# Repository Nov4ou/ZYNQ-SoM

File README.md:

# ZYNQ-SoM

An open-source Zynq-7000 system-on-module, designed in KiCad. The Rev B boards have been assembled and tested.

## Photos

## What is on the board

- AMD/Xilinx XC7Z010-1CLG400C
- 512 MiB DDR3 (Micron MT41K256M16)
- 32 MiB QSPI NOR flash (Winbond W25Q256)
- 33.3333 MHz PS reference clock
- Two Panasonic AXK580137YG 80-pin board-to-board receptacles
- 50 mm × 40 mm, 6-layer PCB
- Separate PL Bank 34 and Bank 35 I/O voltage inputs
- 5 V module input with on-board power rails

The bottom-side silkscreen labels the connectors `PL IO` and `PS IO`. J402 carries PS MIO, configuration/JTAG, and PL Bank 35. J403 carries PL Bank 34 and module power-related pins.

## Files

```text
hardware/kicad/        KiCad project, schematic, PCB, symbols, footprints, and 3D models
docs/                  Schematic PDF, schematic page images, photos, and connector lengths
production/bom/        BOM exported from KiCad
production/gerbers/    Gerber and drill files
```

Open [hardware/kicad/ZYNQ-SoM.kicad_pro](hardware/kicad/ZYNQ-SoM.kicad_pro) with KiCad 10.0 or newer. Project symbols, footprints, and 3D models are referenced relative to `${KIPRJMOD}`, so no global custom-library setup is required.

## Useful files

- [SoM connector routing lengths](docs/connector-routing-lengths.md)
- [Machine-readable routing lengths](docs/connector-routing-lengths.csv)
- [Schematic PDF](docs/ZYNQ-SoM-schematic.pdf)
- [Gerber ZIP](production/gerbers/ZYNQ-SoM.zip)
- [BOM](production/bom/ZYNQ-SoM.csv)

The connector length table is for carrier-board length matching. It uses KiCad Net Inspector style lengths for the SoM-side routing; connector contact length and carrier-board routing are not included.

## Notes

- The checked-in Gerbers are the fabrication files for this revision.
- Review the KiCad source before ordering boards or changing parts.

## License

Released under the CERN Open Hardware Licence Version 2 - Permissive (`CERN-OHL-P-2.0`). See [LICENSE](LICENSE).

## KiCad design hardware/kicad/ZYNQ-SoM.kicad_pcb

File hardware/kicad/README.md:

# KiCad source

Open `ZYNQ-SoM.kicad_pro` with KiCad 10.0 or newer.

- `ZYNQ-SoM.kicad_sch` is the root schematic.
- `sheets/` contains the hierarchical schematic sheets.
- `ZYNQ-SoM.kicad_pcb` is the six-layer board layout.
- `ZYNQ-SoM.kicad_dru` contains project design rules.
- `lib/` contains the project-local KiCad symbols, `.pretty` footprint library, and 3D models.

Library tables use `${KIPRJMOD}` paths, so the project should be portable after cloning.

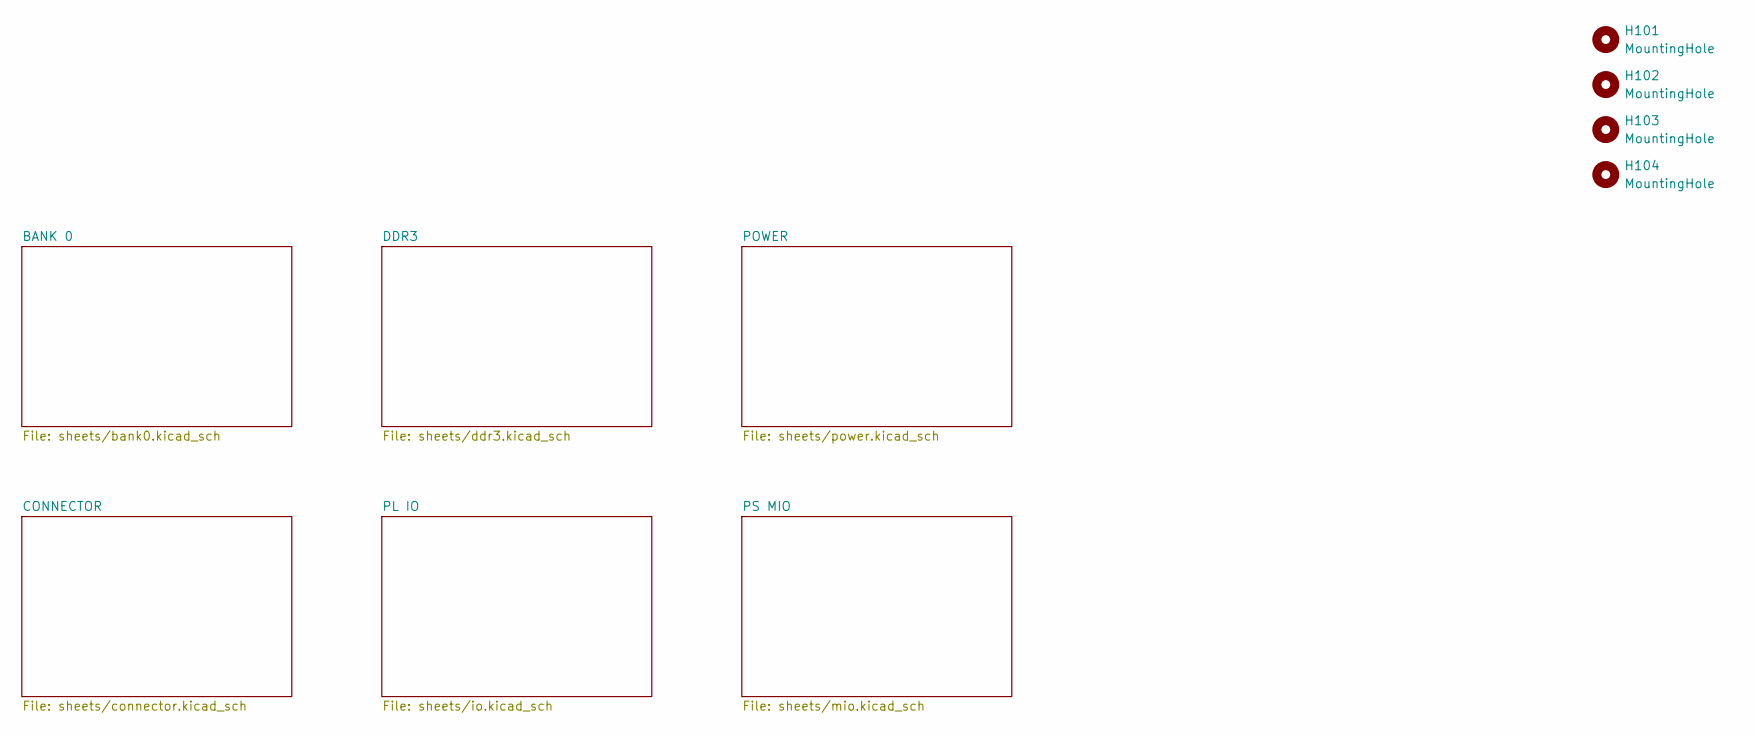
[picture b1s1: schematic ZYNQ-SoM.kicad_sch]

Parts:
H101, H102, H103, H104: MountingHole; MountingHole_2.2mm_M2

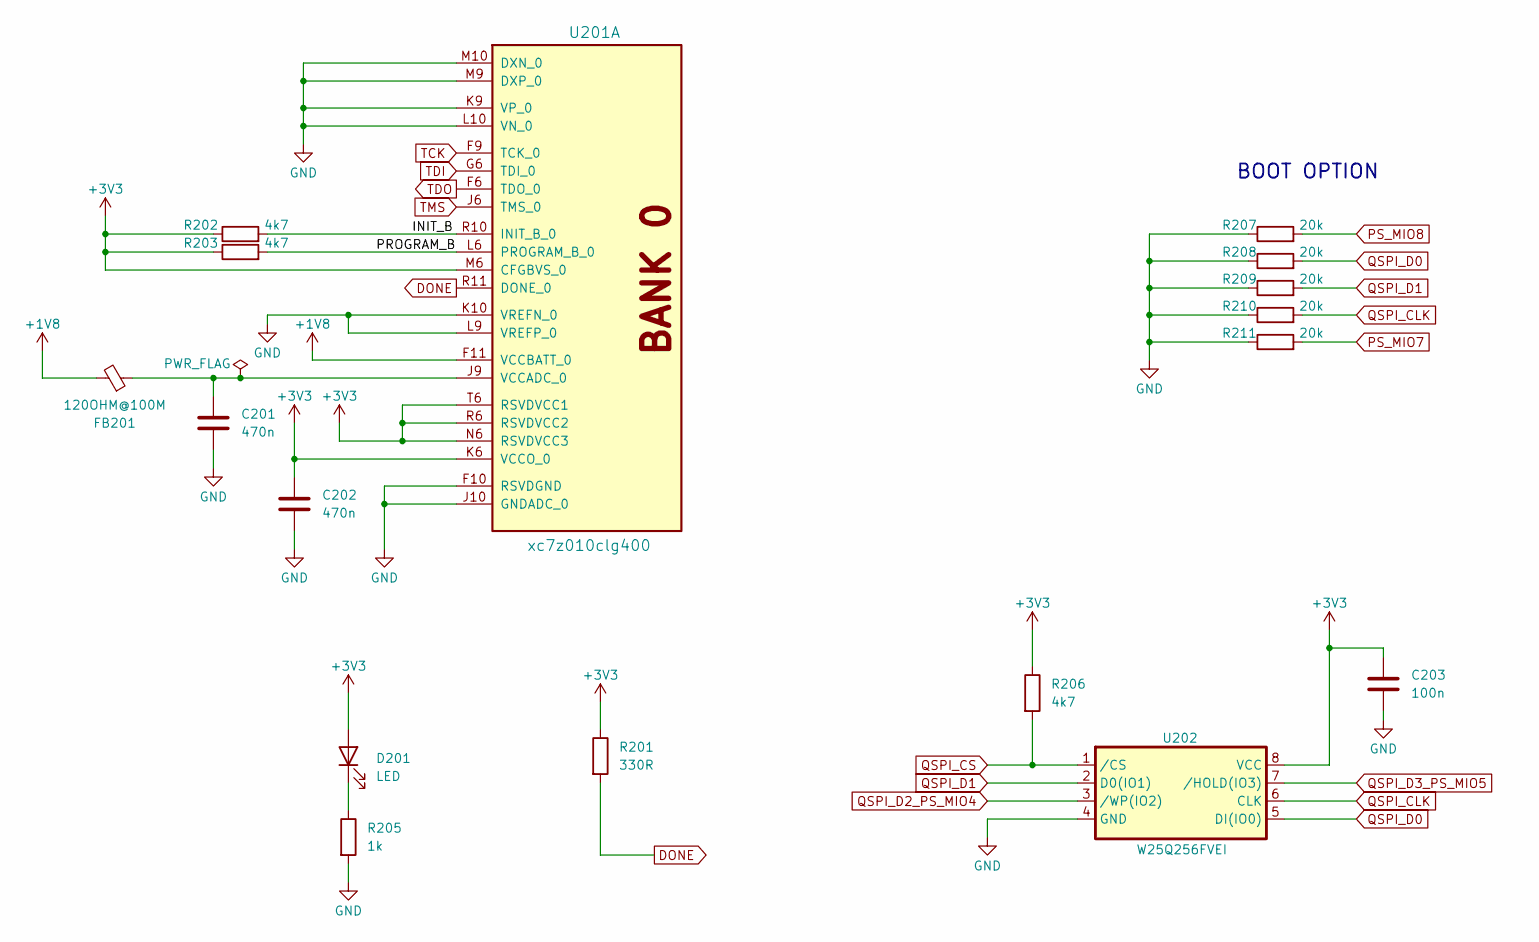
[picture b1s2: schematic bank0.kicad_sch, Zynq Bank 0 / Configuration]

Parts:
C201, C202: 470n; C_0402_1005Metric
C203: 100n; C_0402_1005Metric
D201: LED; LED_0603_1608Metric
FB201: 120OHM@100M; L_0402_1005Metric
R201: 330R; R_0402_1005Metric
R202, R203, R206: 4k7; R_0402_1005Metric
R205: 1k; R_0402_1005Metric
R207, R208, R209, R210, R211: 20k; R_0402_1005Metric
U201: xc7z010clg400; Xilinx_CLG400
U202: W25Q256FVEI; SON127P800X600X80-9N-D

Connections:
+1V8: FB201.2, U201.F11 (VCCBATT_0); also elsewhere on the board
+3V3: C202.1, C203.1, D201.2 (A), R201.1, R202.1, R203.1, R206.1, U201.K6 (VCCO_0), U201.M6 (CFGBVS_0), U201.N6 (RSVDVCC3), U201.R6 (RSVDVCC2), U201.T6 (RSVDVCC1), U202.8 (VCC); also elsewhere on the board
/BANK 0/INIT_B: R202.2, U201.R10 (INIT_B_0)
/BANK 0/PROGRAM_B: R203.2, U201.L6 (PROGRAM_B_0)
DONE: R201.2, U201.R11 (DONE_0); also elsewhere on the board
GND: C201.2, C202.2, C203.2, R205.2, R207.1, R208.1, R209.1, R210.1, R211.1, U201.F10 (RSVDGND), U201.J10 (GNDADC_0), U201.K9 (VP_0), U201.K10 (VREFN_0), U201.L9 (VREFP_0), U201.L10 (VN_0), U201.M9 (DXP_0), U201.M10 (DXN_0), U202.4 (GND), U202.9 (GND); also elsewhere on the board
unnamed: D201.1 (K), R205.1
unnamed: C201.1, FB201.1, U201.J9 (VCCADC_0)
PS_MIO7: R211.2; also elsewhere on the board
PS_MIO8: R207.2; also elsewhere on the board
QSPI_CLK: R210.2, U202.6 (CLK); also elsewhere on the board
QSPI_CS: R206.2, U202.1 (/CS); also elsewhere on the board
QSPI_D0: R208.2, U202.5 (DI(IO0)); also elsewhere on the board
QSPI_D1: R209.2, U202.2 (D0(IO1)); also elsewhere on the board
QSPI_D2_PS_MIO4: U202.3 (/WP(IO2)); also elsewhere on the board
QSPI_D3_PS_MIO5: U202.7 (/HOLD(IO3)); also elsewhere on the board
TCK: U201.F9 (TCK_0); also elsewhere on the board
TDI: U201.G6 (TDI_0); also elsewhere on the board
TDO: U201.F6 (TDO_0); also elsewhere on the board
TMS: U201.J6 (TMS_0); also elsewhere on the board

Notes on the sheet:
BOOT OPTION

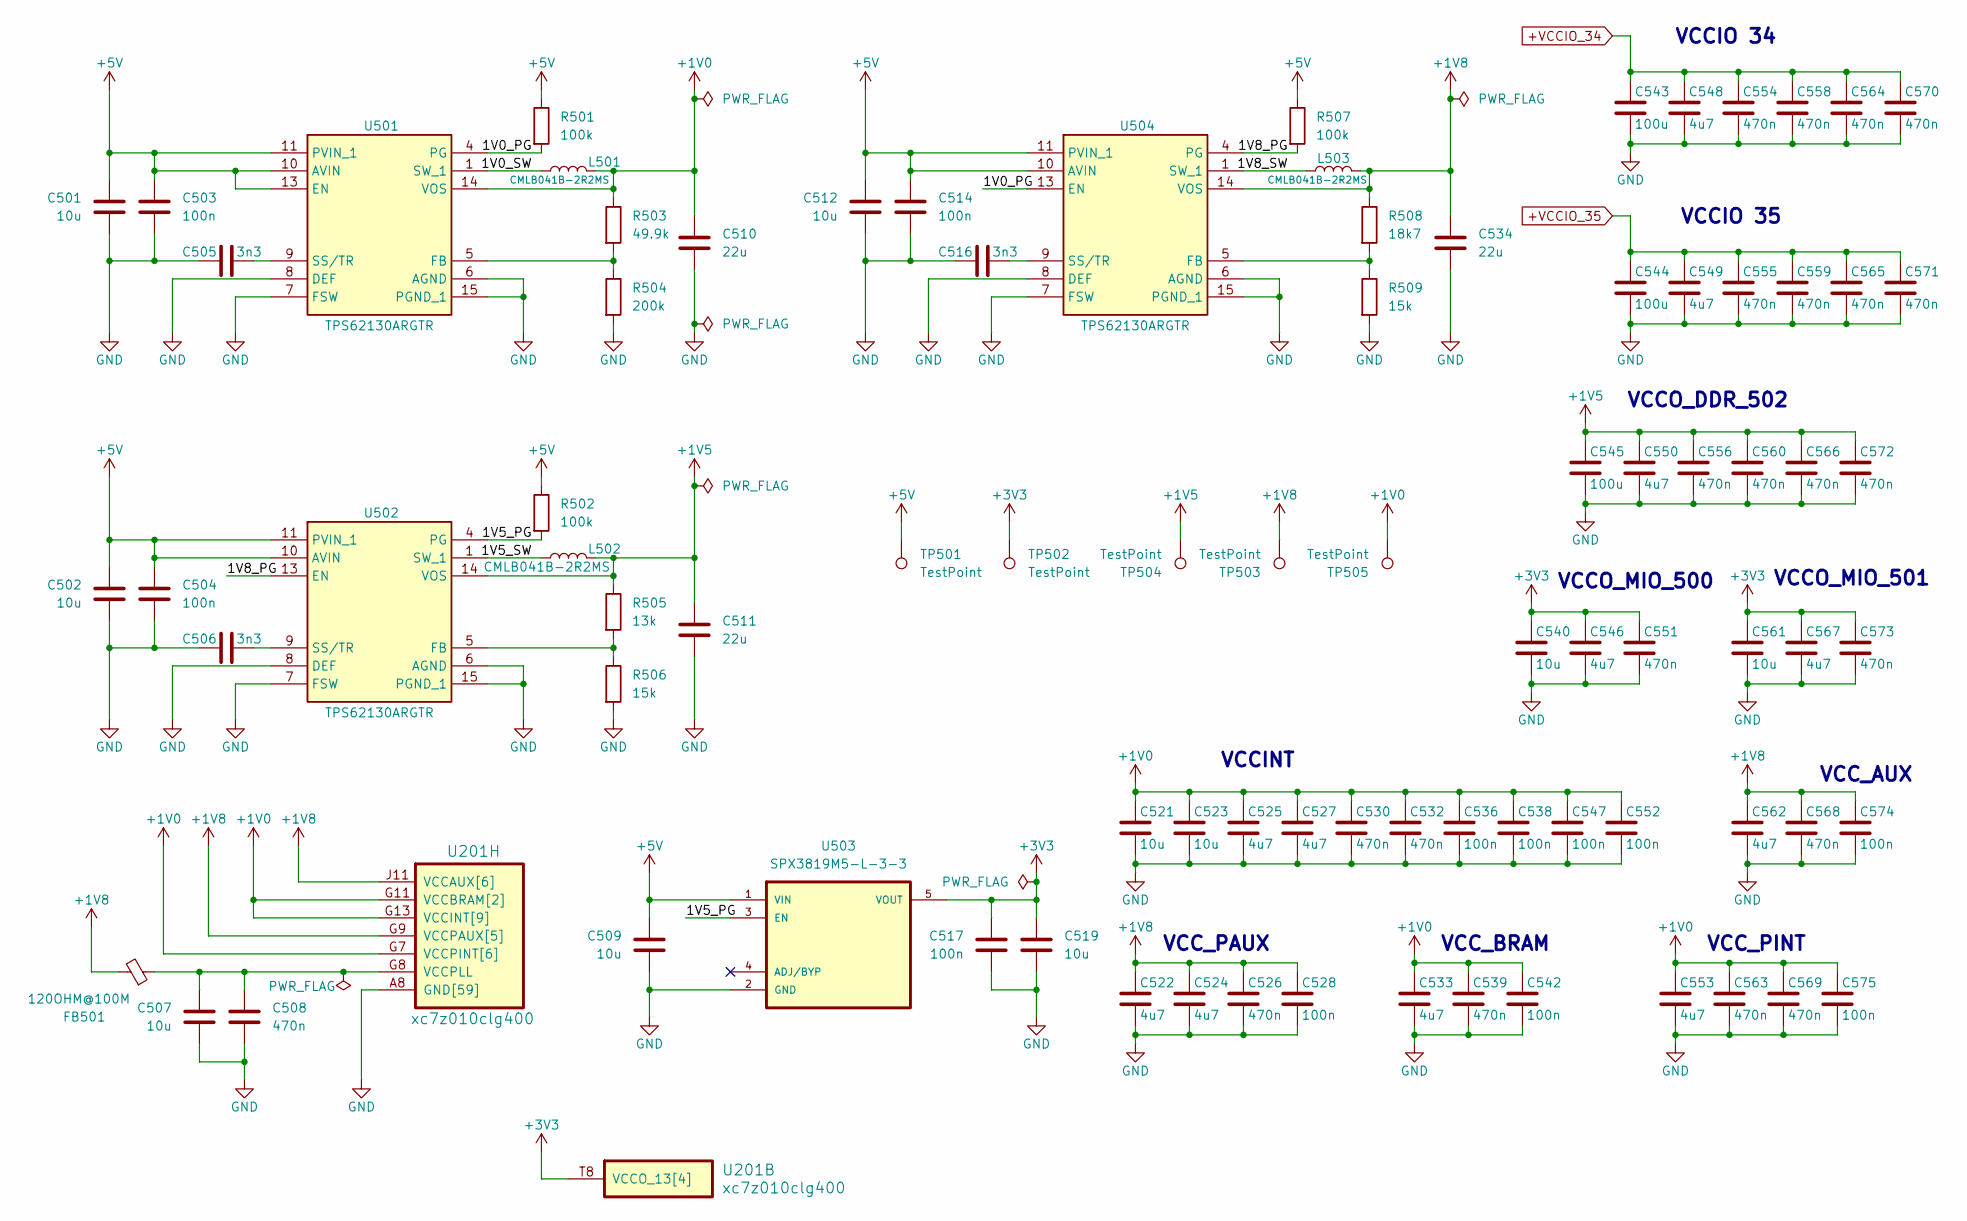
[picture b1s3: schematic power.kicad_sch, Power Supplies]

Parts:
C501, C502, C509, C512, C519, C521, C523, C561: 10u; C_0805_2012Metric
C503, C504, C514, C517, C528, C536, C538, C542, C547, C552, C574, C575: 100n; C_0402_1005Metric
C505, C506, C516: 3n3; C_0402_1005Metric
C507, C540: 10u; C_0603_1608Metric
C508, C526, C530, C532, C539, C551, C554, C555, C556, C558, C559, C560, C563, C564, C565, C566, C568, C569, C570, C571, C572, C573: 470n; C_0402_1005Metric
C510, C511, C534: 22u; C_0805_2012Metric
C522, C524, C525, C527, C533, C546, C548, C549, C550, C553, C562, C567: 4u7; C_0603_1608Metric
C543, C544, C545: 100u; C_1206_3216Metric
FB501: 120OHM@100M; L_0402_1005Metric
L501, L502, L503: CMLB041B-2R2MS; IND_CMLB041B-1R0MS
R501, R502, R507: 100k; R_0402_1005Metric
R503: 49.9k; R_0402_1005Metric
R504: 200k; R_0402_1005Metric
R505: 13k; R_0402_1005Metric
R506, R509: 15k; R_0402_1005Metric
R508: 18k7; R_0402_1005Metric
TP501, TP502, TP503, TP504, TP505: TestPoint; TestPoint_Pad_D1.0mm
U201: xc7z010clg400; Xilinx_CLG400
U501, U502, U504: TPS62130ARGTR; QFN50P300X300X100-17N-D; Manufacturer_Part_Number TPS62130ARGTR; Mouser Part Number 595-TPS62130ARGTR
U503: SPX3819M5-L-3-3; MPN SPX3819M5-L-3-3

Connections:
+1V0: C510.1, C521.1, C523.1, C525.1, C527.1, C530.1, C532.1, C533.1, C536.1, C538.1, C539.1, C542.1, C547.1, C552.1, C553.1, C563.1, C569.1, C575.1, L501.2, R503.1, TP505.1 (1_1), U201.G7 (VCCPINT[6]), U201.G11 (VCCBRAM[2]), U201.G13 (VCCINT[9]), U201.H10 (VCCBRAM[2]), U201.H12 (VCCINT[9]), U201.J7 (VCCPINT[6]), U201.J13 (VCCINT[9]), U201.K12 (VCCINT[9]), U201.L7 (VCCPINT[6]), U201.L13 (VCCINT[9]), U201.M12 (VCCINT[9]), U201.N7 (VCCPINT[6]), U201.N13 (VCCINT[9]), U201.P8 (VCCPINT[6]), U201.P12 (VCCINT[9]), U201.R7 (VCCPINT[6]), U201.R13 (VCCINT[9]), U501.14 (VOS)
+1V5: C511.1, C545.1, C550.1, C556.1, C560.1, C566.1, C572.1, L502.2, R505.1, TP504.1 (1_1), U502.14 (VOS); also elsewhere on the board
+1V8: C522.1, C524.1, C526.1, C528.1, C534.1, C562.1, C568.1, C574.1, FB501.2, L503.2, R508.1, TP503.1 (1_1), U201.F8 (VCCPAUX[5]), U201.G9 (VCCPAUX[5]), U201.H8 (VCCPAUX[5]), U201.J11 (VCCAUX[6]), U201.K8 (VCCPAUX[5]), U201.L11 (VCCAUX[6]), U201.M8 (VCCPAUX[5]), U201.N9 (VCCAUX[6]), U201.N11 (VCCAUX[6]), U201.P10 (VCCAUX[6]), U201.R9 (VCCAUX[6]), U504.14 (VOS); also elsewhere on the board
+3V3: C517.1, C519.1, C540.1, C546.1, C551.1, C561.1, C567.1, C573.1, TP502.1 (1_1), U201.T8 (VCCO_13[4]), U201.U11 (VCCO_13[4]), U201.W7 (VCCO_13[4]), U201.Y10 (VCCO_13[4]), U503.5 (VOUT); also elsewhere on the board
+5V: C501.1, C502.1, C503.1, C504.1, C509.1, C512.1, C514.1, R501.1, R502.1, R507.1, TP501.1 (1_1), U501.10 (AVIN), U501.11 (PVIN_1), U501.12 (PVIN_2), U501.13 (EN), U502.10 (AVIN), U502.11 (PVIN_1), U502.12 (PVIN_2), U503.1 (VIN), U504.10 (AVIN), U504.11 (PVIN_1), U504.12 (PVIN_2); also elsewhere on the board
+VCCIO_34: C543.1, C548.1, C554.1, C558.1, C564.1, C570.1; also elsewhere on the board
+VCCIO_35: C544.1, C549.1, C555.1, C559.1, C565.1, C571.1; also elsewhere on the board
/POWER/1V0_PG: R501.2, U501.4 (PG), U504.13 (EN)
/POWER/1V0_SW: L501.1, U501.1 (SW_1), U501.2 (SW_2), U501.3 (SW_3)
/POWER/1V5_PG: R502.2, U502.4 (PG), U503.3 (EN)
/POWER/1V5_SW: L502.1, U502.1 (SW_1), U502.2 (SW_2), U502.3 (SW_3)
/POWER/1V8_PG: R507.2, U502.13 (EN), U504.4 (PG)
/POWER/1V8_SW: L503.1, U504.1 (SW_1), U504.2 (SW_2), U504.3 (SW_3)
GND: C501.2, C502.2, C503.2, C504.2, C505.1, C506.1, C507.2, C508.2, C509.2, C510.2, C511.2, C512.2, C514.2, C516.1, C517.2, C519.2, C521.2, C522.2, C523.2, C524.2, C525.2, C526.2, C527.2, C528.2, C530.2, C532.2, C533.2, C534.2, C536.2, C538.2, C539.2, C540.2, C542.2, C543.2, C544.2, C545.2, C546.2, C547.2, C548.2, C549.2, C550.2, C551.2, C552.2, C553.2, C554.2, C555.2, C556.2, C558.2, C559.2, C560.2, C561.2, C562.2, C563.2, C564.2, C565.2, C566.2, C567.2, C568.2, C569.2, C570.2, C571.2, C572.2, C573.2, C574.2, C575.2, R504.2, R506.2, R509.2, U201.A8 (GND[59]), U201.A18 (GND[59]), U201.B1 (GND[59]), U201.B11 (GND[59]), U201.C4 (GND[59]), U201.C9 (GND[59]), U201.C14 (GND[59]), U201.D17 (GND[59]), U201.E10 (GND[59]), U201.E20 (GND[59]), U201.F3 (GND[59]), U201.F7 (GND[59]), U201.G10 (GND[59]), U201.G12 (GND[59]), U201.G16 (GND[59]), U201.H7 (GND[59]), U201.H9 (GND[59]), U201.H11 (GND[59]), U201.H13 (GND[59]), U201.H19 (GND[59]), U201.J2 (GND[59]), U201.J8 (GND[59]), U201.J12 (GND[59]), U201.K5 (GND[59]), U201.K7 (GND[59]), U201.K11 (GND[59]), U201.K13 (GND[59]), U201.K15 (GND[59]), U201.L8 (GND[59]), U201.L12 (GND[59]), U201.L18 (GND[59]), U201.M1 (GND[59]), U201.M7 (GND[59]), U201.M11 (GND[59]), U201.M13 (GND[59]), U201.N4 (GND[59]), U201.N8 (GND[59]), U201.N10 (GND[59]), U201.N12 (GND[59]), U201.N14 (GND[59]), U201.P7 (GND[59]), U201.P9 (GND[59]), U201.P11 (GND[59]), U201.P13 (GND[59]), U201.P17 (GND[59]), U201.R8 (GND[59]), U201.R12 (GND[59]), U201.R20 (GND[59]), U201.T3 (GND[59]), U201.T7 (GND[59]), U201.T13 (GND[59]), U201.U6 (GND[59]), U201.U16 (GND[59]), U201.V9 (GND[59]), U201.V19 (GND[59]), U201.W2 (GND[59]), U201.W12 (GND[59]), U201.Y5 (GND[59]), U201.Y15 (GND[59]), U501.6 (AGND), U501.7 (FSW), U501.8 (DEF), U501.15 (PGND_1), U501.16 (PGND_2), U501.17 (EP), U502.6 (AGND), U502.7 (FSW), U502.8 (DEF), U502.15 (PGND_1), U502.16 (PGND_2), U502.17 (EP), U503.2 (GND), U504.6 (AGND), U504.7 (FSW), U504.8 (DEF), U504.15 (PGND_1), U504.16 (PGND_2), U504.17 (EP); also elsewhere on the board
unnamed: C507.1, C508.1, FB501.1, U201.G8 (VCCPLL)
unnamed: R503.2, R504.1, U501.5 (FB)
unnamed: C505.2, U501.9 (SS/TR)
unnamed: R505.2, R506.1, U502.5 (FB)
unnamed: C506.2, U502.9 (SS/TR)
unnamed: R508.2, R509.1, U504.5 (FB)
unnamed: C516.2, U504.9 (SS/TR)

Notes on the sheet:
VCC_BRAM
VCCINT
VCCO_DDR_502
VCC_PAUX
VCC_PINT
VCCO_MIO_501
VCCIO 35
VCCIO 34
VCC_AUX
VCCO_MIO_500

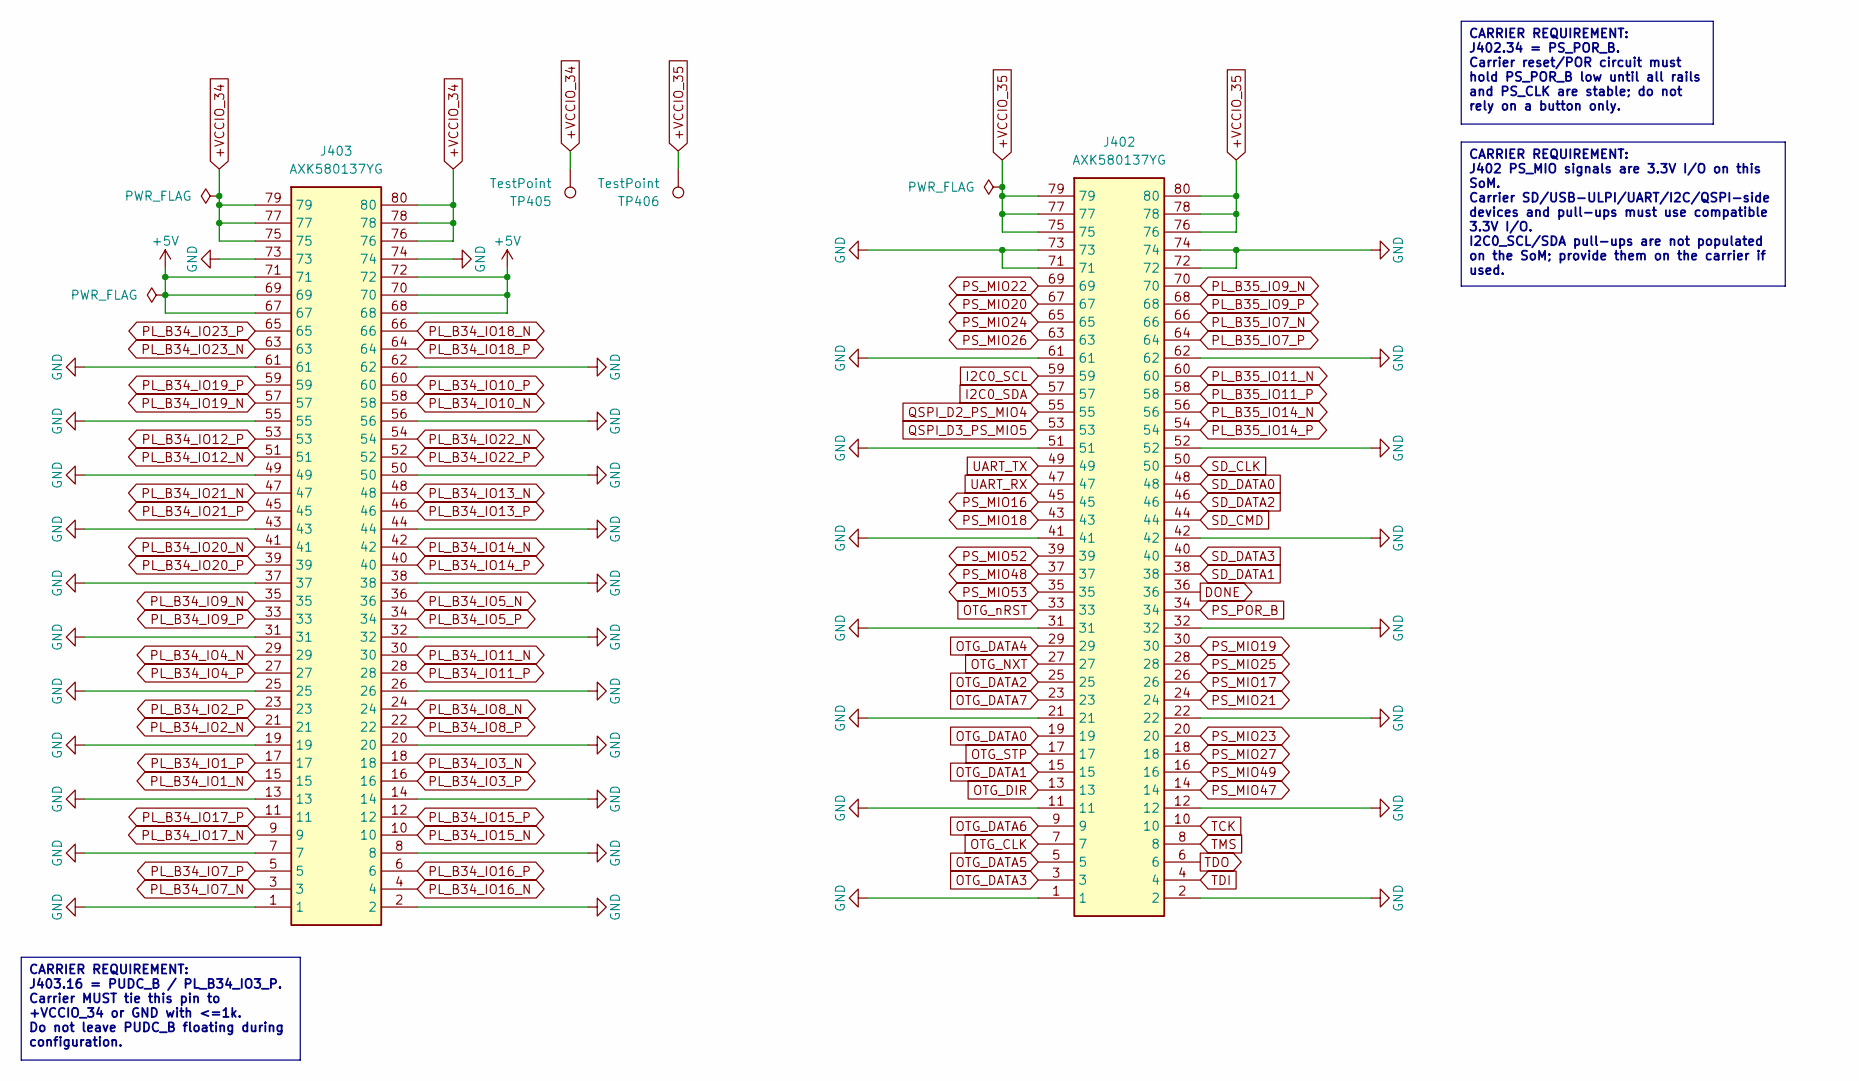
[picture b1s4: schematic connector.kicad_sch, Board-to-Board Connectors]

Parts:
J402, J403: AXK580137YG; Manufacturer_Part_Number AXK580137YG; Mouser Part Number 769-AXK580137YG
TP405, TP406: TestPoint; TestPoint_Pad_D1.0mm

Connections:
+5V: J403.67, J403.68, J403.69, J403.70, J403.71, J403.72; also elsewhere on the board
+VCCIO_34: J403.75, J403.76, J403.77, J403.78, J403.79, J403.80, TP405.1 (1_1); also elsewhere on the board
+VCCIO_35: J402.75, J402.76, J402.77, J402.78, J402.79, J402.80, TP406.1 (1_1); also elsewhere on the board
DONE: J402.36; also elsewhere on the board
GND: J402.1, J402.2, J402.11, J402.12, J402.21, J402.22, J402.31, J402.32, J402.41, J402.42, J402.51, J402.52, J402.61, J402.62, J402.71, J402.72, J402.73, J402.74, J403.1, J403.2, J403.7, J403.8, J403.13, J403.14, J403.19, J403.20, J403.25, J403.26, J403.31, J403.32, J403.37, J403.38, J403.43, J403.44, J403.49, J403.50, J403.55, J403.56, J403.61, J403.62, J403.73, J403.74; also elsewhere on the board
I2C0_SCL: J402.59; also elsewhere on the board
I2C0_SDA: J402.57; also elsewhere on the board
OTG_CLK: J402.7; also elsewhere on the board
OTG_DATA0: J402.19; also elsewhere on the board
OTG_DATA1: J402.15; also elsewhere on the board
OTG_DATA2: J402.25; also elsewhere on the board
OTG_DATA3: J402.3; also elsewhere on the board
OTG_DATA4: J402.29; also elsewhere on the board
OTG_DATA5: J402.5; also elsewhere on the board
OTG_DATA6: J402.9; also elsewhere on the board
OTG_DATA7: J402.23; also elsewhere on the board
OTG_DIR: J402.13; also elsewhere on the board
OTG_NXT: J402.27; also elsewhere on the board
OTG_STP: J402.17; also elsewhere on the board
OTG_nRST: J402.33; also elsewhere on the board
PL_B34_IO1_N: J403.15; also elsewhere on the board
PL_B34_IO1_P: J403.17; also elsewhere on the board
PL_B34_IO2_N: J403.21; also elsewhere on the board
PL_B34_IO2_P: J403.23; also elsewhere on the board
PL_B34_IO3_N: J403.18; also elsewhere on the board
PL_B34_IO3_P: J403.16; also elsewhere on the board
PL_B34_IO4_N: J403.29; also elsewhere on the board
PL_B34_IO4_P: J403.27; also elsewhere on the board
PL_B34_IO5_N: J403.36; also elsewhere on the board
PL_B34_IO5_P: J403.34; also elsewhere on the board
PL_B34_IO7_N: J403.3; also elsewhere on the board
PL_B34_IO7_P: J403.5; also elsewhere on the board
PL_B34_IO8_N: J403.24; also elsewhere on the board
PL_B34_IO8_P: J403.22; also elsewhere on the board
PL_B34_IO9_N: J403.35; also elsewhere on the board
PL_B34_IO9_P: J403.33; also elsewhere on the board
PL_B34_IO10_N: J403.58; also elsewhere on the board
PL_B34_IO10_P: J403.60; also elsewhere on the board
PL_B34_IO11_N: J403.30; also elsewhere on the board
PL_B34_IO11_P: J403.28; also elsewhere on the board
PL_B34_IO12_N: J403.51; also elsewhere on the board
PL_B34_IO12_P: J403.53; also elsewhere on the board
PL_B34_IO13_N: J403.48; also elsewhere on the board
PL_B34_IO13_P: J403.46; also elsewhere on the board
PL_B34_IO14_N: J403.42; also elsewhere on the board
PL_B34_IO14_P: J403.40; also elsewhere on the board
PL_B34_IO15_N: J403.10; also elsewhere on the board
PL_B34_IO15_P: J403.12; also elsewhere on the board
PL_B34_IO16_N: J403.4; also elsewhere on the board
PL_B34_IO16_P: J403.6; also elsewhere on the board
PL_B34_IO17_N: J403.9; also elsewhere on the board
PL_B34_IO17_P: J403.11; also elsewhere on the board
PL_B34_IO18_N: J403.66; also elsewhere on the board
PL_B34_IO18_P: J403.64; also elsewhere on the board
PL_B34_IO19_N: J403.57; also elsewhere on the board
PL_B34_IO19_P: J403.59; also elsewhere on the board
PL_B34_IO20_N: J403.41; also elsewhere on the board
PL_B34_IO20_P: J403.39; also elsewhere on the board
PL_B34_IO21_N: J403.47; also elsewhere on the board
PL_B34_IO21_P: J403.45; also elsewhere on the board
PL_B34_IO22_N: J403.54; also elsewhere on the board
PL_B34_IO22_P: J403.52; also elsewhere on the board
PL_B34_IO23_N: J403.63; also elsewhere on the board
PL_B34_IO23_P: J403.65; also elsewhere on the board
PL_B35_IO7_N: J402.66; also elsewhere on the board
PL_B35_IO7_P: J402.64; also elsewhere on the board
PL_B35_IO9_N: J402.70; also elsewhere on the board
PL_B35_IO9_P: J402.68; also elsewhere on the board
PL_B35_IO11_N: J402.60; also elsewhere on the board
PL_B35_IO11_P: J402.58; also elsewhere on the board
PL_B35_IO14_N: J402.56; also elsewhere on the board
PL_B35_IO14_P: J402.54; also elsewhere on the board
PS_MIO16: J402.45; also elsewhere on the board
PS_MIO17: J402.26; also elsewhere on the board
PS_MIO18: J402.43; also elsewhere on the board
PS_MIO19: J402.30; also elsewhere on the board
PS_MIO20: J402.67; also elsewhere on the board
PS_MIO21: J402.24; also elsewhere on the board
PS_MIO22: J402.69; also elsewhere on the board
PS_MIO23: J402.20; also elsewhere on the board
PS_MIO24: J402.65; also elsewhere on the board
PS_MIO25: J402.28; also elsewhere on the board
PS_MIO26: J402.63; also elsewhere on the board
PS_MIO27: J402.18; also elsewhere on the board
PS_MIO47: J402.14; also elsewhere on the board
PS_MIO48: J402.37; also elsewhere on the board
PS_MIO49: J402.16; also elsewhere on the board
PS_MIO52: J402.39; also elsewhere on the board
PS_MIO53: J402.35; also elsewhere on the board
PS_POR_B: J402.34; also elsewhere on the board
QSPI_D2_PS_MIO4: J402.55; also elsewhere on the board
QSPI_D3_PS_MIO5: J402.53; also elsewhere on the board
SD_CLK: J402.50; also elsewhere on the board
SD_CMD: J402.44; also elsewhere on the board
SD_DATA0: J402.48; also elsewhere on the board
SD_DATA1: J402.38; also elsewhere on the board
SD_DATA2: J402.46; also elsewhere on the board
SD_DATA3: J402.40; also elsewhere on the board
TCK: J402.10; also elsewhere on the board
TDI: J402.4; also elsewhere on the board
TDO: J402.6; also elsewhere on the board
TMS: J402.8; also elsewhere on the board
UART_RX: J402.47; also elsewhere on the board
UART_TX: J402.49; also elsewhere on the board

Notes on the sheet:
CARRIER REQUIREMENT: J403.16 = PUDC_B / PL_B34_IO3_P. Carrier MUST tie this pin to +VCCIO_34 or GND with <=1k. Do not leave PUDC_B floating during configuration.
CARRIER REQUIREMENT: J402.34 = PS_POR_B. Carrier reset/POR circuit must hold PS_POR_B low until all rails and PS_CLK are stable; do not rely on a button only.
CARRIER REQUIREMENT: J402 PS_MIO signals are 3.3V I/O on this SoM. Carrier SD/USB-ULPI/UART/I2C/QSPI-side devices and pull-ups must use compatible 3.3V I/O. I2C0_SCL/SDA pull-ups are not populated on the SoM; provide them on the carrier if used.

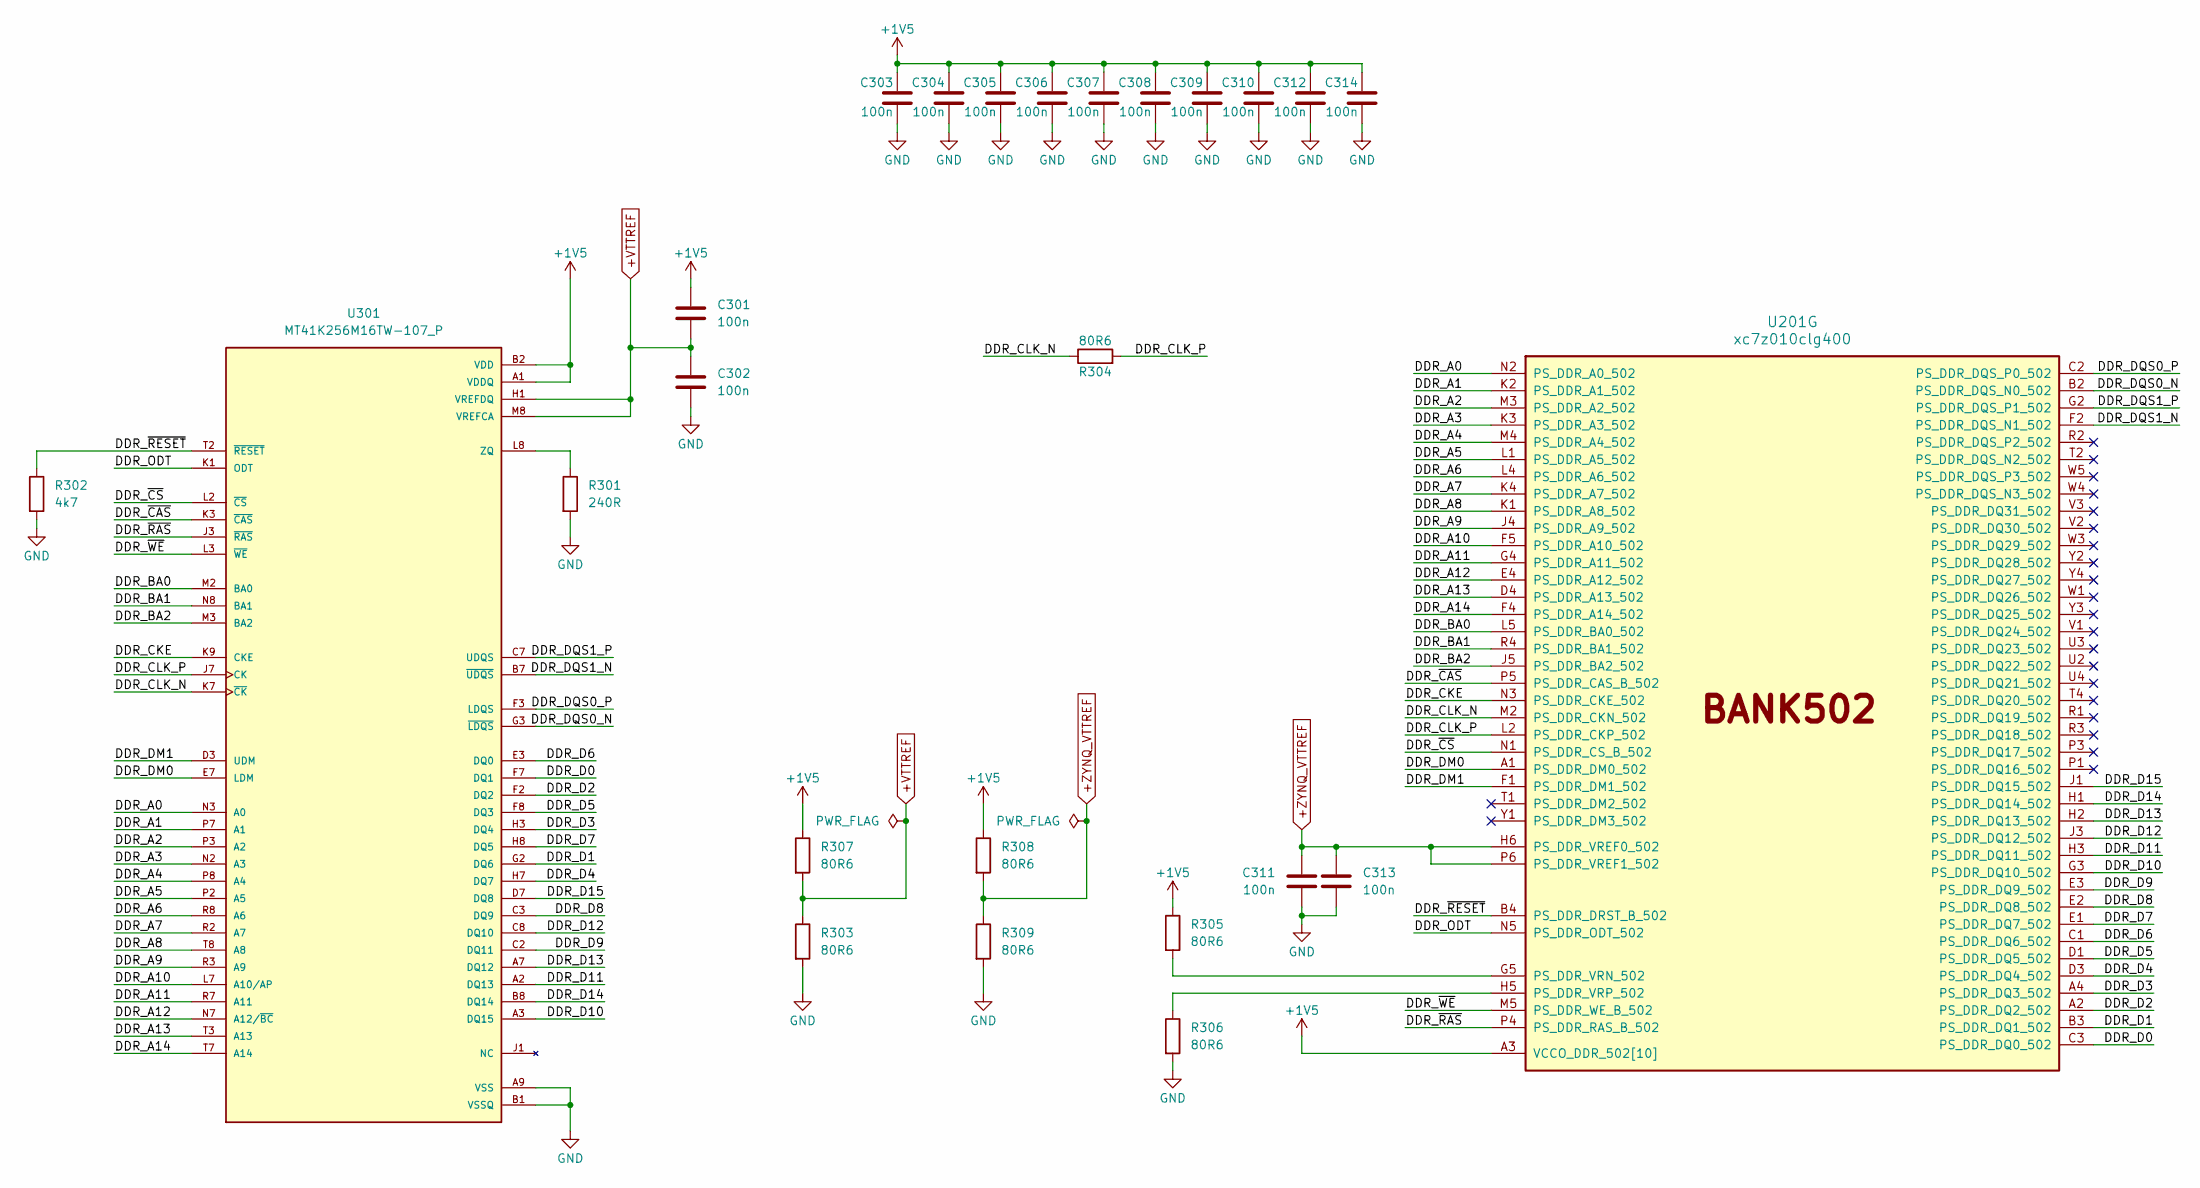
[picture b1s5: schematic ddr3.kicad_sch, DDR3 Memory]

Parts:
C301, C302, C303, C304, C305, C306, C307, C308, C309, C310, C311, C312, C313, C314: 100n; C_0402_1005Metric
R301: 240R; R_0402_1005Metric
R302: 4k7; R_0402_1005Metric
R303, R304, R305, R306, R307, R308, R309: 80R6; R_0402_1005Metric
U201: xc7z010clg400; Xilinx_CLG400
U301: MT41K256M16TW-107_P; BGA96C80P9X16_1400X800X120; PARTREV P

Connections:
+1V5: C301.1, C303.1, C304.1, C305.1, C306.1, C307.1, C308.1, C309.1, C310.1, C312.1, C314.1, R305.1, R307.1, R308.1, U201.A3 (VCCO_DDR_502[10]), U201.D2 (VCCO_DDR_502[10]), U201.E5 (VCCO_DDR_502[10]), U201.G1 (VCCO_DDR_502[10]), U201.H4 (VCCO_DDR_502[10]), U201.L3 (VCCO_DDR_502[10]), U201.P2 (VCCO_DDR_502[10]), U201.R5 (VCCO_DDR_502[10]), U201.U1 (VCCO_DDR_502[10]), U201.V4 (VCCO_DDR_502[10]), U301.A1 (VDDQ), U301.A8 (VDDQ), U301.B2 (VDD), U301.C1 (VDDQ), U301.C9 (VDDQ), U301.D2 (VDDQ), U301.D9 (VDD), U301.E9 (VDDQ), U301.F1 (VDDQ), U301.G7 (VDD), U301.H2 (VDDQ), U301.H9 (VDDQ), U301.K2 (VDD), U301.K8 (VDD), U301.N1 (VDD), U301.N9 (VDD), U301.R1 (VDD), U301.R9 (VDD); also elsewhere on the board
+VTTREF: C301.2, C302.1, R303.1, R307.2, U301.H1 (VREFDQ), U301.M8 (VREFCA)
+ZYNQ_VTTREF: C311.1, C313.1, R308.2, R309.1, U201.H6 (PS_DDR_VREF0_502), U201.P6 (PS_DDR_VREF1_502)
/DDR3/DDR_A0: U201.N2 (PS_DDR_A0_502), U301.N3 (A0)
/DDR3/DDR_A1: U201.K2 (PS_DDR_A1_502), U301.P7 (A1)
/DDR3/DDR_A2: U201.M3 (PS_DDR_A2_502), U301.P3 (A2)
/DDR3/DDR_A3: U201.K3 (PS_DDR_A3_502), U301.N2 (A3)
/DDR3/DDR_A4: U201.M4 (PS_DDR_A4_502), U301.P8 (A4)
/DDR3/DDR_A5: U201.L1 (PS_DDR_A5_502), U301.P2 (A5)
/DDR3/DDR_A6: U201.L4 (PS_DDR_A6_502), U301.R8 (A6)
/DDR3/DDR_A7: U201.K4 (PS_DDR_A7_502), U301.R2 (A7)
/DDR3/DDR_A8: U201.K1 (PS_DDR_A8_502), U301.T8 (A8)
/DDR3/DDR_A9: U201.J4 (PS_DDR_A9_502), U301.R3 (A9)
/DDR3/DDR_A10: U201.F5 (PS_DDR_A10_502), U301.L7 (A10/AP)
/DDR3/DDR_A11: U201.G4 (PS_DDR_A11_502), U301.R7 (A11)
/DDR3/DDR_A12: U201.E4 (PS_DDR_A12_502), U301.N7 (A12/~BC)
/DDR3/DDR_A13: U201.D4 (PS_DDR_A13_502), U301.T3 (A13)
/DDR3/DDR_A14: U201.F4 (PS_DDR_A14_502), U301.T7 (A14)
/DDR3/DDR_BA0: U201.L5 (PS_DDR_BA0_502), U301.M2 (BA0)
/DDR3/DDR_BA1: U201.R4 (PS_DDR_BA1_502), U301.N8 (BA1)
/DDR3/DDR_BA2: U201.J5 (PS_DDR_BA2_502), U301.M3 (BA2)
/DDR3/DDR_CKE: U201.N3 (PS_DDR_CKE_502), U301.K9 (CKE)
/DDR3/DDR_CLK_N: R304.1, U201.M2 (PS_DDR_CKN_502), U301.K7 (~CK)
/DDR3/DDR_CLK_P: R304.2, U201.L2 (PS_DDR_CKP_502), U301.J7 (CK)
/DDR3/DDR_D0: U201.C3 (PS_DDR_DQ0_502), U301.F7 (DQ1)
/DDR3/DDR_D1: U201.B3 (PS_DDR_DQ1_502), U301.G2 (DQ6)
/DDR3/DDR_D2: U201.A2 (PS_DDR_DQ2_502), U301.F2 (DQ2)
/DDR3/DDR_D3: U201.A4 (PS_DDR_DQ3_502), U301.H3 (DQ4)
/DDR3/DDR_D4: U201.D3 (PS_DDR_DQ4_502), U301.H7 (DQ7)
/DDR3/DDR_D5: U201.D1 (PS_DDR_DQ5_502), U301.F8 (DQ3)
/DDR3/DDR_D6: U201.C1 (PS_DDR_DQ6_502), U301.E3 (DQ0)
/DDR3/DDR_D7: U201.E1 (PS_DDR_DQ7_502), U301.H8 (DQ5)
/DDR3/DDR_D8: U201.E2 (PS_DDR_DQ8_502), U301.C3 (DQ9)
/DDR3/DDR_D9: U201.E3 (PS_DDR_DQ9_502), U301.C2 (DQ11)
/DDR3/DDR_D10: U201.G3 (PS_DDR_DQ10_502), U301.A3 (DQ15)
/DDR3/DDR_D11: U201.H3 (PS_DDR_DQ11_502), U301.A2 (DQ13)
/DDR3/DDR_D12: U201.J3 (PS_DDR_DQ12_502), U301.C8 (DQ10)
/DDR3/DDR_D13: U201.H2 (PS_DDR_DQ13_502), U301.A7 (DQ12)
/DDR3/DDR_D14: U201.H1 (PS_DDR_DQ14_502), U301.B8 (DQ14)
/DDR3/DDR_D15: U201.J1 (PS_DDR_DQ15_502), U301.D7 (DQ8)
/DDR3/DDR_DM0: U201.A1 (PS_DDR_DM0_502), U301.E7 (LDM)
/DDR3/DDR_DM1: U201.F1 (PS_DDR_DM1_502), U301.D3 (UDM)
/DDR3/DDR_DQS0_N: U201.B2 (PS_DDR_DQS_N0_502), U301.G3 (~LDQS)
/DDR3/DDR_DQS0_P: U201.C2 (PS_DDR_DQS_P0_502), U301.F3 (LDQS)
/DDR3/DDR_DQS1_N: U201.F2 (PS_DDR_DQS_N1_502), U301.B7 (~UDQS)
/DDR3/DDR_DQS1_P: U201.G2 (PS_DDR_DQS_P1_502), U301.C7 (UDQS)
/DDR3/DDR_ODT: U201.N5 (PS_DDR_ODT_502), U301.K1 (ODT)
/DDR3/DDR_~CAS: U201.P5 (PS_DDR_CAS_B_502), U301.K3 (~CAS)
/DDR3/DDR_~CS: U201.N1 (PS_DDR_CS_B_502), U301.L2 (~CS)
/DDR3/DDR_~RAS: U201.P4 (PS_DDR_RAS_B_502), U301.J3 (~RAS)
/DDR3/DDR_~RESET: R302.1, U201.B4 (PS_DDR_DRST_B_502), U301.T2 (~RESET)
/DDR3/DDR_~WE: U201.M5 (PS_DDR_WE_B_502), U301.L3 (~WE)
GND: C302.2, C303.2, C304.2, C305.2, C306.2, C307.2, C308.2, C309.2, C310.2, C311.2, C312.2, C313.2, C314.2, R301.2, R302.2, R303.2, R306.2, R309.2, U301.A9 (VSS), U301.B1 (VSSQ), U301.B3 (VSS), U301.B9 (VSSQ), U301.D1 (VSSQ), U301.D8 (VSSQ), U301.E1 (VSS), U301.E2 (VSSQ), U301.E8 (VSSQ), U301.F9 (VSSQ), U301.G1 (VSSQ), U301.G8 (VSS), U301.G9 (VSSQ), U301.J2 (VSS), U301.J8 (VSS), U301.M1 (VSS), U301.M9 (VSS), U301.P1 (VSS), U301.P9 (VSS), U301.T1 (VSS), U301.T9 (VSS); also elsewhere on the board
unnamed: R305.2, U201.G5 (PS_DDR_VRN_502)
unnamed: R306.1, U201.H5 (PS_DDR_VRP_502)
unnamed: R301.1, U301.L8 (ZQ)
